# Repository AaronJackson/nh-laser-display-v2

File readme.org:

[[.github/workflows/kicad.yaml][file:https://github.com/AaronJackson/nh-laser-display-v2/actions/workflows/kicad.yaml/badge.svg]]

This is an updated version of [[https://github.com/NottingHack/instrumentation-arduino/tree/main/LaserDisplay][LaserDisplay]] for Nottingham Hackspace
after the previous one failed for a few reasons (Arduino Due issues,
broken solder joints after a fall, etc). The previous version was on a
perf board so I decided to make a PCB. I also decided to include a
WizNet, which I haven't tested yet.

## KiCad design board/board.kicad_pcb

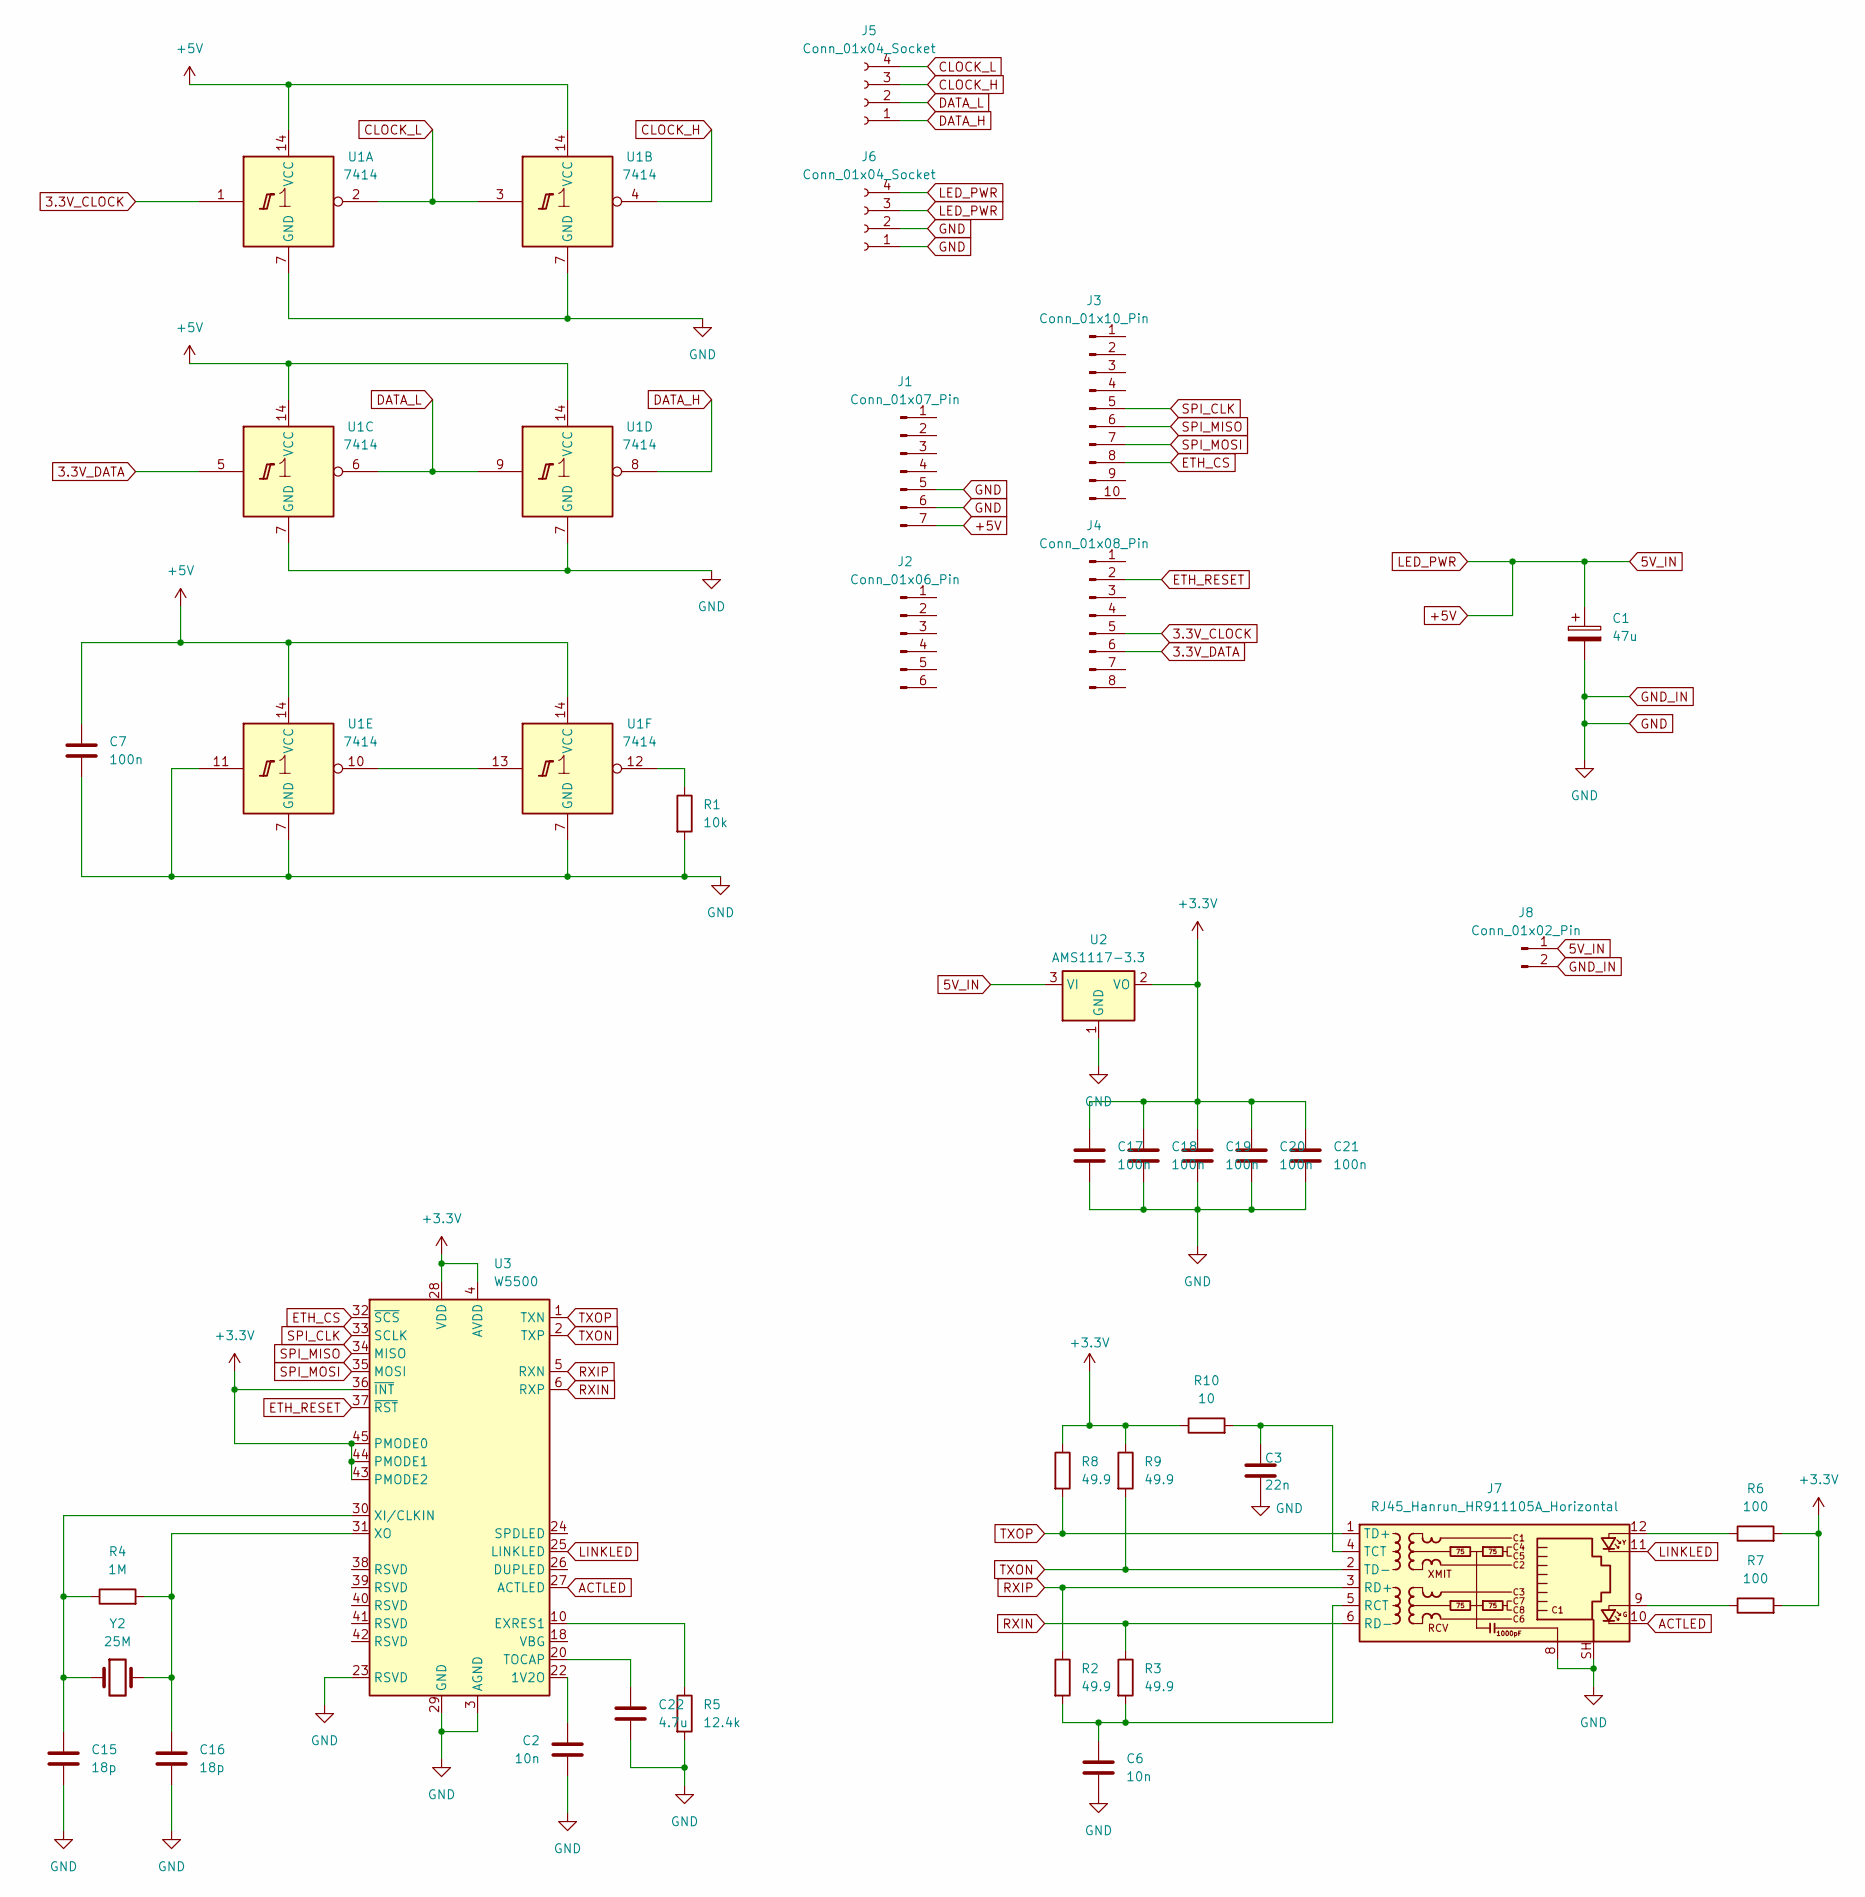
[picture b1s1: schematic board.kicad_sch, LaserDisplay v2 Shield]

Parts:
C1: 47u; CP_Radial_D5.0mm_P2.00mm
C2, C6: 10n; C_0603_1608Metric
C3: 22n; C_0603_1608Metric
C7, C17, C18, C19, C20, C21: 100n; C_0603_1608Metric
C15, C16: 18p; C_0603_1608Metric
C22: 4.7u; C_0603_1608Metric
J1: Conn_01x07_Pin; PinHeader_1x07_P2.54mm_Vertical
J2: Conn_01x06_Pin; PinHeader_1x06_P2.54mm_Vertical
J3: Conn_01x10_Pin; PinHeader_1x10_P2.54mm_Vertical
J4: Conn_01x08_Pin; PinHeader_1x08_P2.54mm_Vertical
J5, J6: Conn_01x04_Socket; TE_MATE-N-LOK_350211-1_1x04_P5.08mm_Vertical
J7: RJ45_Hanrun_HR911105A_Horizontal
J8: Conn_01x02_Pin; TerminalBlock_WAGO_236-103_1x03_P5.00mm_45Degree
R1: 10k; R_0603_1608Metric
R2, R3, R8, R9: 49.9; R_0603_1608Metric
R4: 1M; R_0603_1608Metric
R5: 12.4k; R_0603_1608Metric
R6, R7: 100; R_0603_1608Metric
R10: 10; R_0603_1608Metric
U1: 7414; SOIC-14_3.9x8.7mm_P1.27mm
U2: AMS1117-3.3; SOT-223-3_TabPin2
U3: W5500; LQFP-48_7x7mm_P0.5mm
Y2: 25M; Crystal_SMD_5032-2Pin_5.0x3.2mm

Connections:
3.3V_CLOCK: J4.5, U1.1
3.3V_DATA: J4.6, U1.5
+3.3V: C17.1, C18.1, C19.1, C20.1, C21.1, R6.2, R7.2, R8.1, R9.1, R10.1, U2.2 (VO), U3.4 (AVDD), U3.8 (AVDD), U3.11 (AVDD), U3.15 (AVDD), U3.17 (AVDD), U3.21 (AVDD), U3.28 (VDD), U3.36 (~INT), U3.43 (PMODE2), U3.44 (PMODE1), U3.45 (PMODE0)
+5V: C1.1, C7.1, J1.7, J6.3, J6.4, J8.1, U1.14 (VCC), U2.3 (VI)
ACTLED: J7.10, U3.27 (ACTLED)
CLOCK_H: J5.3, U1.4
CLOCK_L: J5.4, U1.2, U1.3
DATA_H: J5.1, U1.8
DATA_L: J5.2, U1.6, U1.9
ETH_CS: J3.8, U3.32 (~SCS)
ETH_RESET: J4.2, U3.37 (~RST)
GND: C1.2, C2.2, C3.2, C6.1, C7.2, C15.2, C16.2, C17.2, C18.2, C19.2, C20.2, C21.2, C22.2, J1.5, J1.6, J6.1, J6.2, J7.8, J7.SH, J8.2, R1.2, R5.2, U1.7 (GND), U1.11, U2.1 (GND), U3.3 (AGND), U3.9 (AGND), U3.14 (AGND), U3.16 (AGND), U3.19 (AGND), U3.23 (RSVD), U3.29 (GND), U3.48 (AGND)
LINKLED: J7.11, U3.25 (LINKLED)
unnamed: J7.9, R7.1
unnamed: J7.12, R6.1
unnamed: C6.2, J7.5 (RCT), R2.2, R3.2
unnamed: C3.1, J7.4 (TCT), R10.2
unnamed: R1.1, U1.12
unnamed: U1.10, U1.13
unnamed: C2.1, U3.22 (1V2O)
unnamed: R5.1, U3.10 (EXRES1)
unnamed: C22.1, U3.20 (TOCAP)
unnamed: C15.1, R4.1, U3.30 (XI/CLKIN), Y2.1
unnamed: C16.1, R4.2, U3.31 (XO), Y2.2
RXIN: J7.6 (RD-), R3.1, U3.6 (RXP)
RXIP: J7.3 (RD+), R2.1, U3.5 (RXN)
SPI_CLK: J3.5, U3.33 (SCLK)
SPI_MISO: J3.6, U3.34 (MISO)
SPI_MOSI: J3.7, U3.35 (MOSI)
TXON: J7.2 (TD-), R9.2, U3.2 (TXP)
TXOP: J7.1 (TD+), R8.2, U3.1 (TXN)

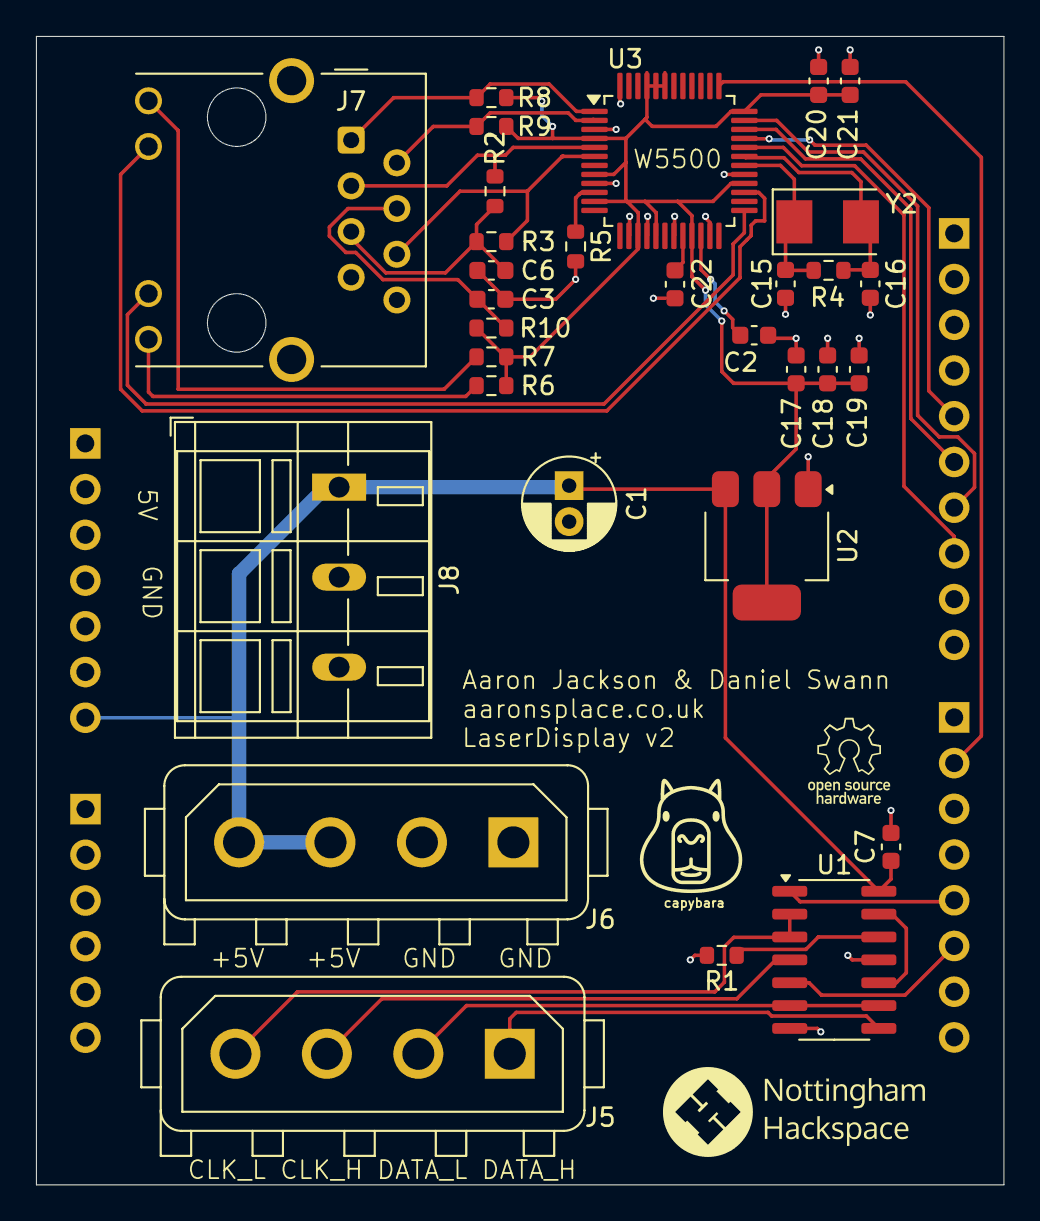
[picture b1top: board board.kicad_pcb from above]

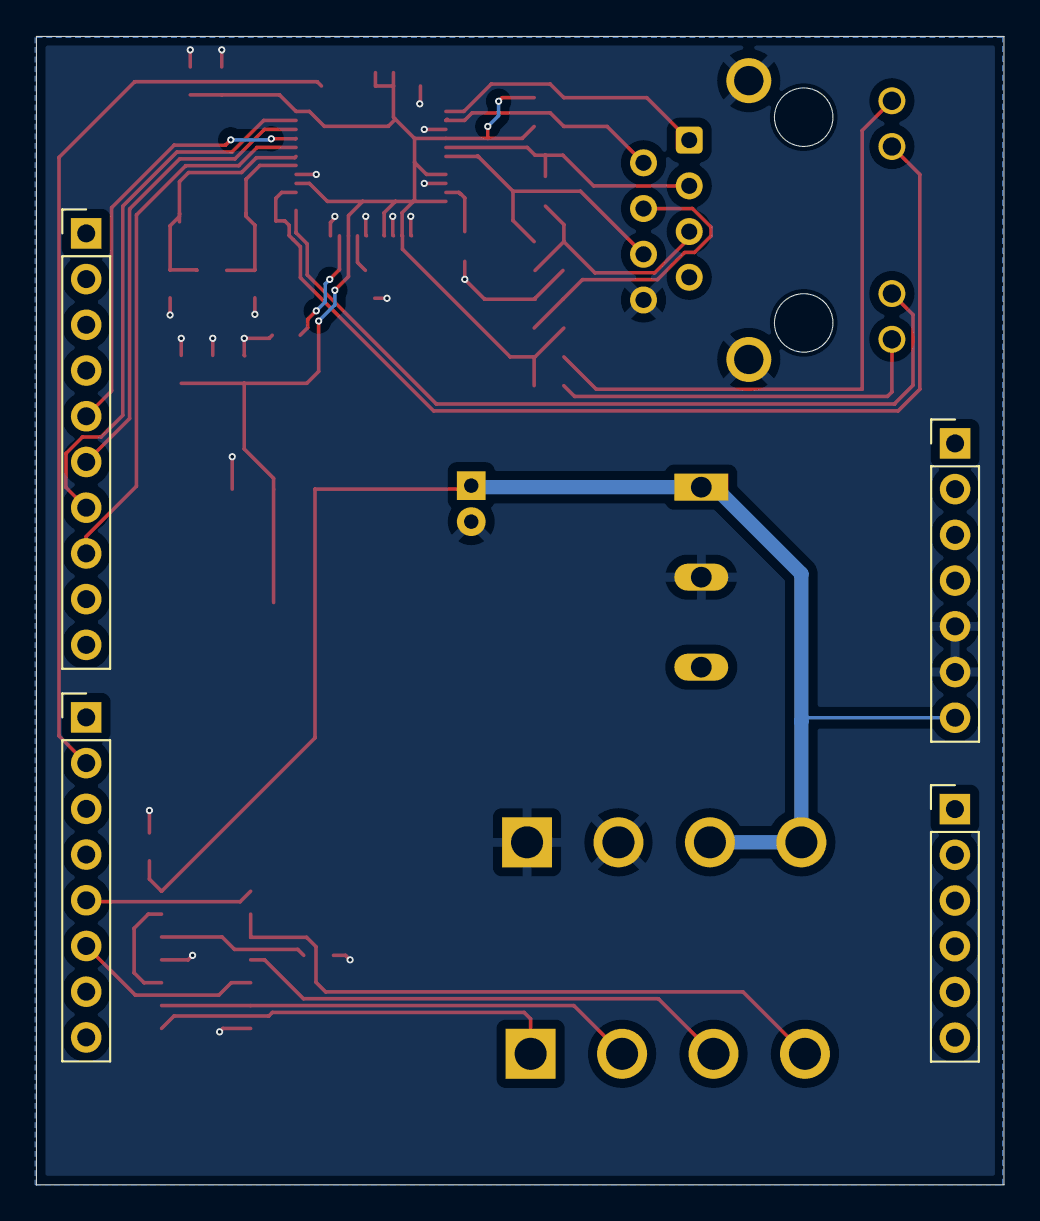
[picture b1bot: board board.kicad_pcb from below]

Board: 2 copper layers, 53.8 x 63.8 mm, 35 parts (4 on the bottom side), 31 nets.

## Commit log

2024-05-16 first commit, early stages
2024-05-16 Small changes prior to ordering
2024-05-17 test
2024-05-17 small fixes
2024-05-17 try to echo output
2024-05-17 Add ERC ignores for various floating pins
2024-05-17 Remove unnecessary echo test
2024-05-17 readme
2024-05-27 Removal of C4 and C5 from Ethernet rx lines
2024-05-27 Changes post PCB build
2024-06-09 Changes for the Studio Display
2024-06-12 Add status monitoring
2024-09-25 Changes for Electronics Area display
2024-09-25 Fix doorbell message
2024-10-21 Version to display random stuff for events
2025-06-08 Add DS18B20 for Laser chiller temperature
2025-06-24 Add interrupt for geiger counter
2025-06-24 Add enclosure for CAJOE geiger counter
